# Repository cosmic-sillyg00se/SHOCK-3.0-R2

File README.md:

# SHOCK-3.0-R2
(7/14/2025) I finally discovered manufacturer datasheets! Kudos to past me, I maanaged to cram even more components onto an even smaller board WIHTOUT sacrificing aesthetics. I say this because it didn't work.

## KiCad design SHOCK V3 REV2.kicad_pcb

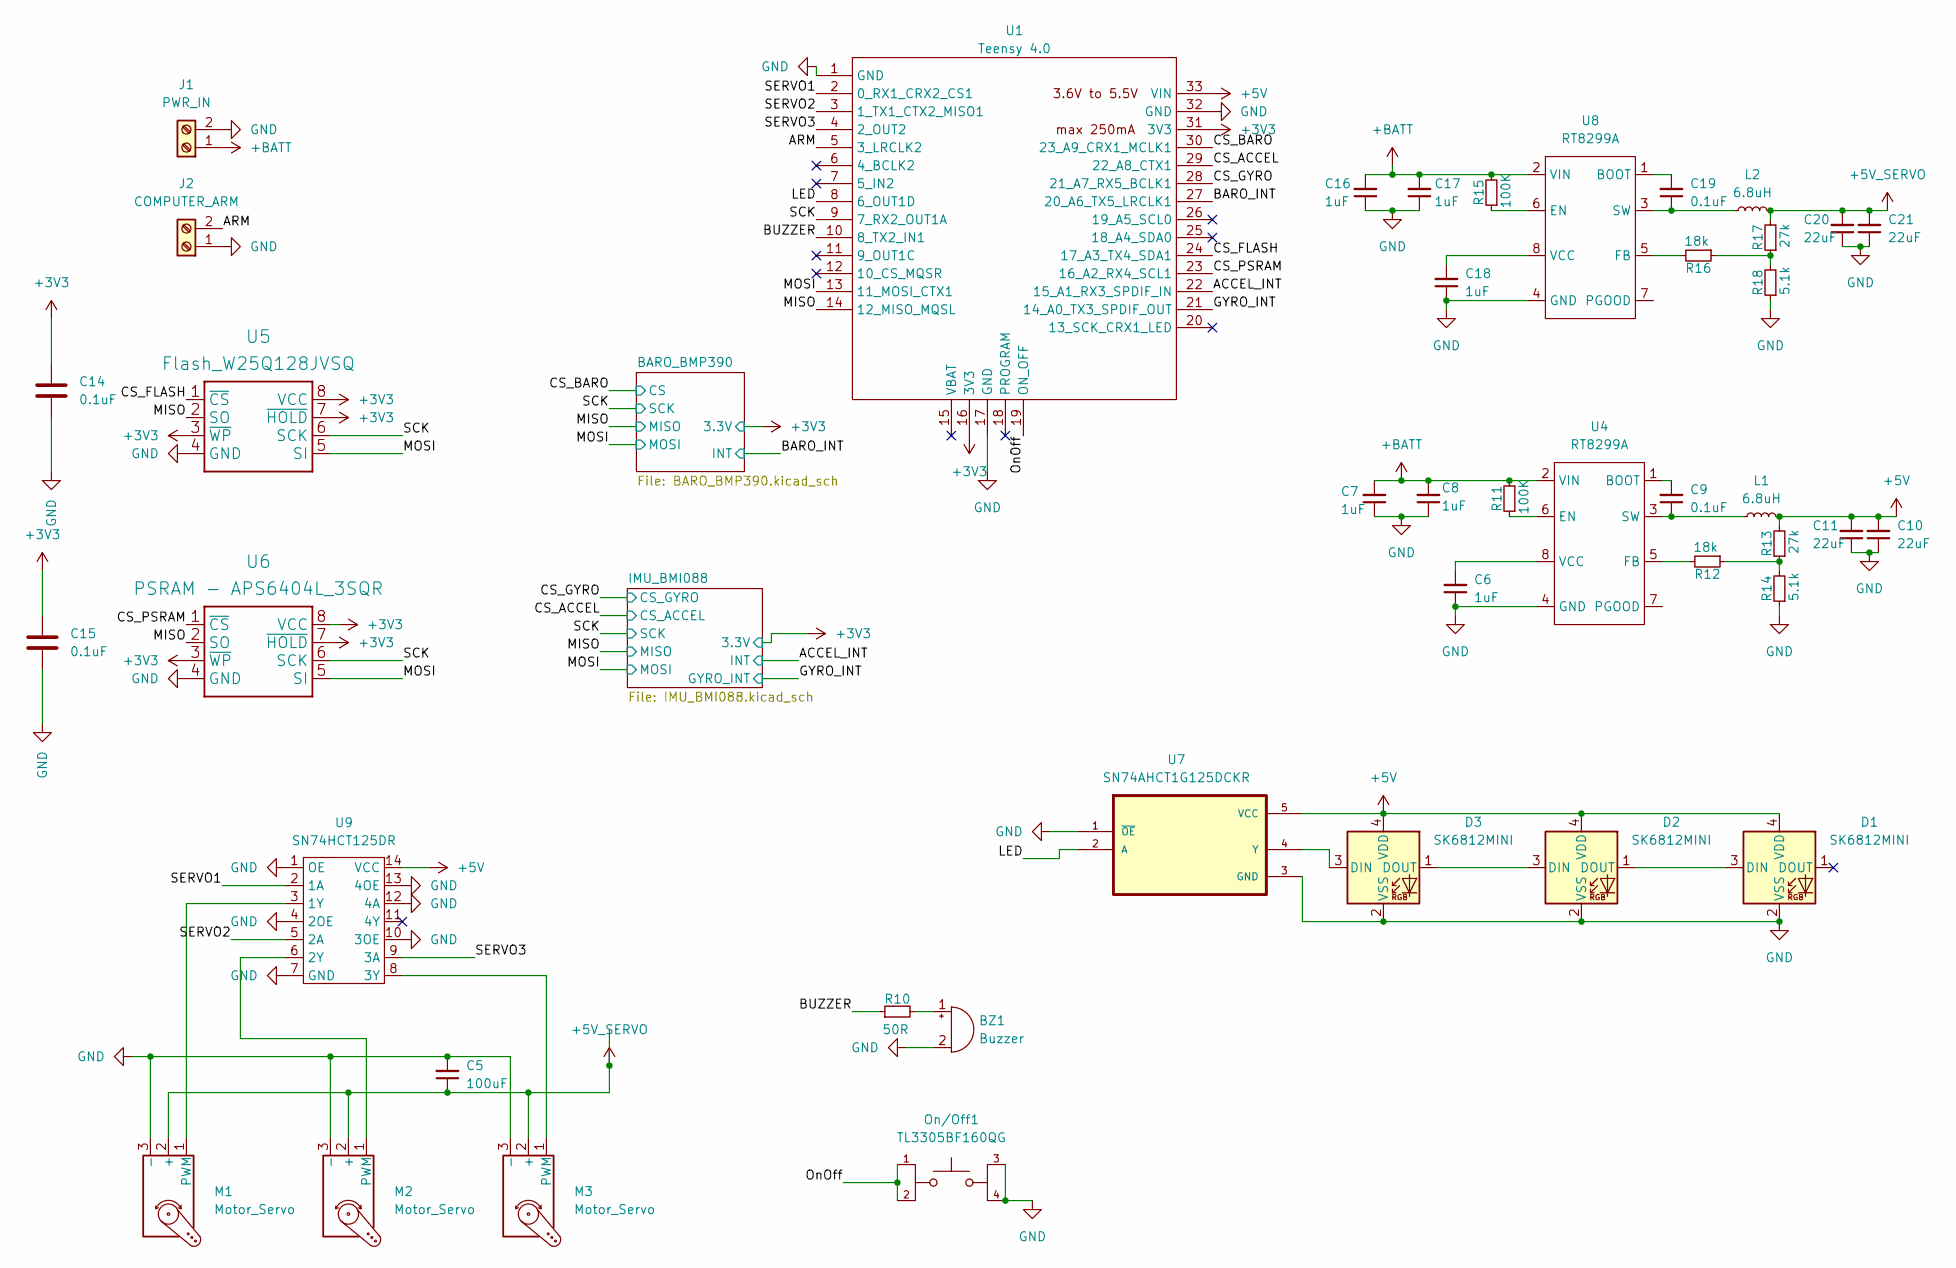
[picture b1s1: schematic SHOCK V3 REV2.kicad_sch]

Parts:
BZ1: Buzzer; Buzzer_TDK_PS1240P02BT_D12.2mm_H6.5mm
C5: 100uF; CP_Elec_8x10.5
C6, C7, C8, C16, C17, C18: 1uF; C_0603_1608Metric_Pad1.08x0.95mm_HandSolder
C9, C14, C15, C19: 0.1uF; C_0603_1608Metric_Pad1.08x0.95mm_HandSolder
C10, C11, C20, C21: 22uF; C_0603_1608Metric_Pad1.08x0.95mm_HandSolder
D1, D2, D3: SK6812MINI; LED_SK6805_PLCC4_2.4x2.7mm_P1.3mm
J1: PWR_IN; TerminalBlock_MaiXu_MX126-5.0-02P_1x02_P5.00mm
J2: COMPUTER_ARM; TerminalBlock_MaiXu_MX126-5.0-02P_1x02_P5.00mm
L1, L2: 6.8uH; L_0603_1608Metric_Pad1.05x0.95mm_HandSolder
M1, M2, M3: Motor_Servo; PinHeader_1x03_P2.54mm_Vertical
On/Off1: TL3305BF160QG; SW_TL3305BF160QG; PARTREV C
R10: 50R; R_0603_1608Metric_Pad0.98x0.95mm_HandSolder
R11, R15: 100K; R_0603_1608Metric_Pad0.98x0.95mm_HandSolder
R12, R16: 18k; R_0603_1608Metric_Pad0.98x0.95mm_HandSolder
R13, R17: 27k; R_0603_1608Metric_Pad0.98x0.95mm_HandSolder
R14, R18: 5.1k; R_0603_1608Metric_Pad0.98x0.95mm_HandSolder
U1: Teensy 4.0; Teensy4.0
U4, U8: RT8299A; SOIC-8_5.3x6.2mm_P1.27mm
U5: Flash_W25Q128JVSQ; SOIC127P790X216-8N
U6: PSRAM - APS6404L_3SQR; SOIC127P790X216-8N
U7: SN74AHCT1G125DCKR; SOT65P210X110-5N
U9: SN74HCT125DR; SOIC-14_3.9x8.7mm_P1.27mm

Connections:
+3V3: C14.1, C15.1, U1.16 (3V3), U1.31 (3V3), U5.3 (~WP), U5.7 (~HOLD), U5.8 (VCC), U6.3 (~WP), U6.7 (~HOLD), U6.8 (VCC); also elsewhere on the board
+5V: C10.2, C11.2, D1.4 (VDD), D2.4 (VDD), D3.4 (VDD), L1.2, R13.2, U1.33 (VIN), U7.5 (VCC), U9.14 (VCC)
+5V_SERVO: C5.1, C20.2, C21.2, L2.2, M1.2 (+), M2.2 (+), M3.2 (+), R17.2
+BATT: C7.2, C8.2, C16.2, C17.2, J1.1, R11.2, R15.2, U4.2 (VIN), U8.2 (VIN)
/ACCEL_INT: U1.22 (15_A1_RX3_SPDIF_IN); also elsewhere on the board
/ARM: J2.2, U1.5 (3_LRCLK2)
/BARO_INT: U1.27 (20_A6_TX5_LRCLK1); also elsewhere on the board
/BUZZER: R10.1, U1.10 (8_TX2_IN1)
/CS_ACCEL: U1.29 (22_A8_CTX1); also elsewhere on the board
/CS_BARO: U1.30 (23_A9_CRX1_MCLK1); also elsewhere on the board
/CS_FLASH: U1.24 (17_A3_TX4_SDA1), U5.1 (~CS)
/CS_GYRO: U1.28 (21_A7_RX5_BCLK1); also elsewhere on the board
/CS_PSRAM: U1.23 (16_A2_RX4_SCL1), U6.1 (~CS)
/GYRO_INT: U1.21 (14_A0_TX3_SPDIF_OUT); also elsewhere on the board
/LED: U1.8 (6_OUT1D), U7.2 (A)
/MISO: U1.14 (12_MISO_MQSL), U5.2 (SO), U6.2 (SO); also elsewhere on the board
/MOSI: U1.13 (11_MOSI_CTX1), U5.5 (SI), U6.5 (SI); also elsewhere on the board
/OnOff: On/Off1.1, On/Off1.2, U1.19 (ON_OFF)
/SCK: U1.9 (7_RX2_OUT1A), U5.6 (SCK), U6.6 (SCK); also elsewhere on the board
/SERVO1: U1.2 (0_RX1_CRX2_CS1), U9.2 (1A)
/SERVO2: U1.3 (1_TX1_CTX2_MISO1), U9.5 (2A)
/SERVO3: U1.4 (2_OUT2), U9.9 (3A)
GND: BZ1.2 (-), C5.2, C6.1, C7.1, C8.1, C10.1, C11.1, C14.2, C15.2, C16.1, C17.1, C18.1, C20.1, C21.1, D1.2 (VSS), D2.2 (VSS), D3.2 (VSS), J1.2, J2.1, M1.3 (-), M2.3 (-), M3.3 (-), On/Off1.3, On/Off1.4, R14.1, R18.1, U1.1 (GND), U1.17 (GND), U1.32 (GND), U4.4 (GND), U5.4 (GND), U6.4 (GND), U7.1 (~OE), U7.3 (GND), U8.4 (GND), U9.1 (OE), U9.4 (2OE), U9.7 (GND), U9.10 (3OE), U9.12 (4A), U9.13 (4OE); also elsewhere on the board
unnamed: BZ1.1 (+), R10.2
unnamed: D1.3 (DIN), D2.1 (DOUT)
unnamed: D2.3 (DIN), D3.1 (DOUT)
unnamed: D3.3 (DIN), U7.4 (Y)
unnamed: M1.1 (PWM), U9.3 (1Y)
unnamed: M2.1 (PWM), U9.6 (2Y)
unnamed: M3.1 (PWM), U9.8 (3Y)
unnamed: R12.1, R13.1, R14.2
unnamed: R16.1, R17.1, R18.2
unnamed: C9.2, U4.1 (BOOT)
unnamed: R11.1, U4.6 (EN)
unnamed: R12.2, U4.5 (FB)
unnamed: C9.1, L1.1, U4.3 (SW)
unnamed: C6.2, U4.8 (VCC)
unnamed: C19.2, U8.1 (BOOT)
unnamed: R15.1, U8.6 (EN)
unnamed: R16.2, U8.5 (FB)
unnamed: C19.1, L2.1, U8.3 (SW)
unnamed: C18.2, U8.8 (VCC)

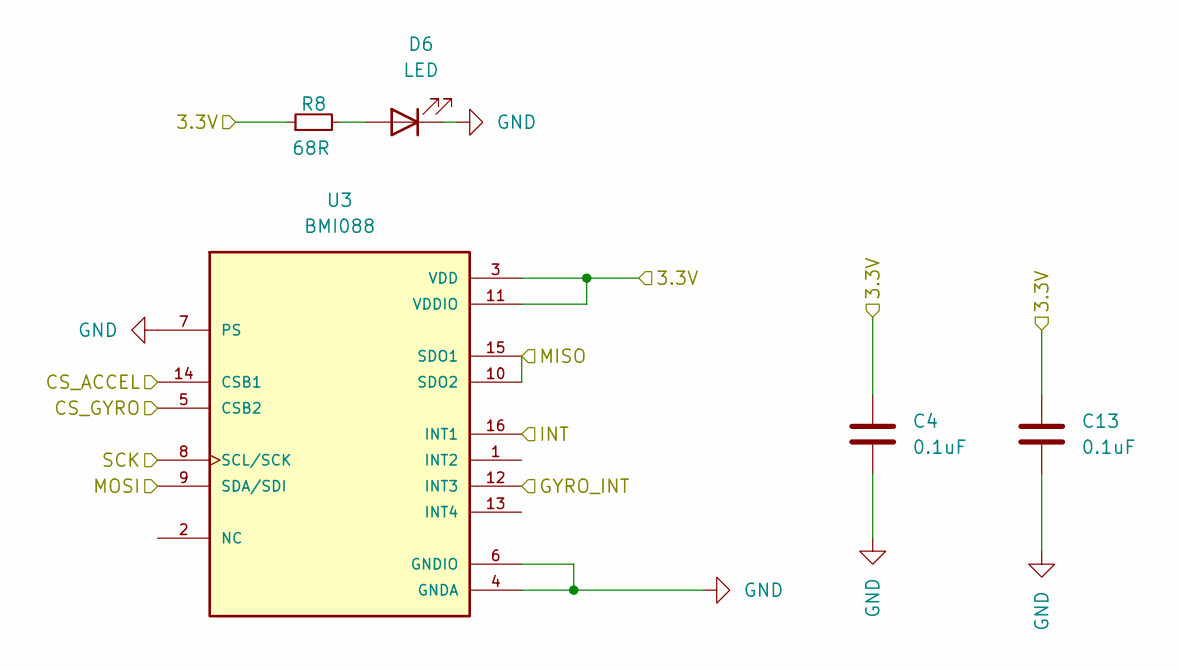
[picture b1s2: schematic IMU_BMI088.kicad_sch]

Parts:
C4, C13: 0.1uF; C_0603_1608Metric_Pad1.08x0.95mm_HandSolder
D6: LED; LED_0603_1608Metric
R8: 68R; R_0603_1608Metric_Pad0.98x0.95mm_HandSolder
U3: BMI088; BMI088SMT

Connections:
+3V3: C4.1, C13.1, R8.1, U3.3 (VDD), U3.11 (VDDIO); also elsewhere on the board
/ACCEL_INT: U3.16 (INT1); also elsewhere on the board
/CS_ACCEL: U3.14 (CSB1); also elsewhere on the board
/CS_GYRO: U3.5 (CSB2); also elsewhere on the board
/GYRO_INT: U3.12 (INT3); also elsewhere on the board
/MISO: U3.10 (SDO2), U3.15 (SDO1); also elsewhere on the board
/MOSI: U3.9 (SDA/SDI); also elsewhere on the board
/SCK: U3.8 (SCL/SCK); also elsewhere on the board
GND: C4.2, C13.2, D6.1 (K), U3.4 (GNDA), U3.6 (GNDIO), U3.7 (PS); also elsewhere on the board
unnamed: D6.2 (A), R8.2

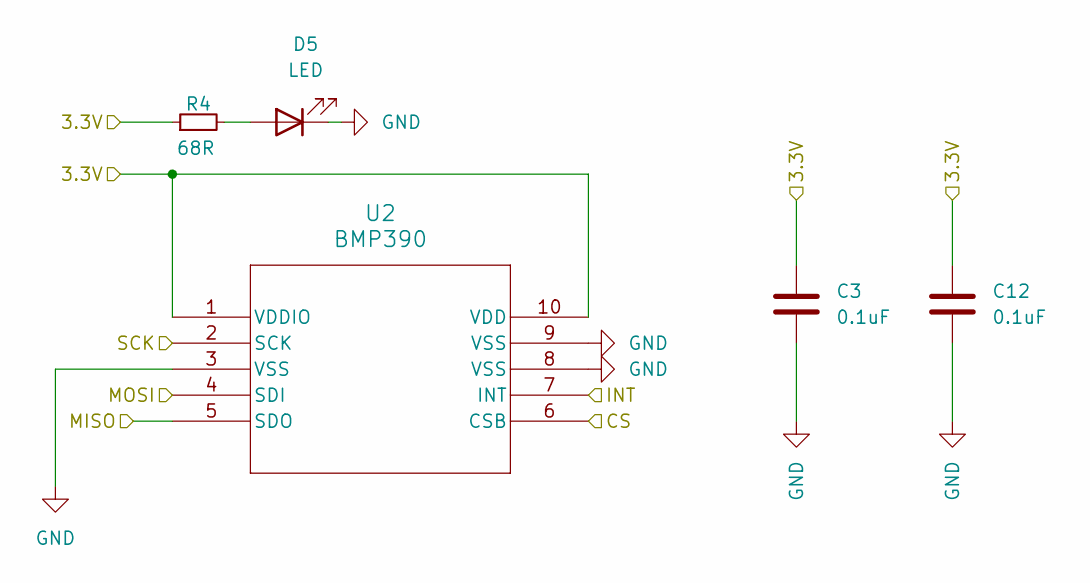
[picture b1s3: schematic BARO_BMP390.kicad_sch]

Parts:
C3, C12: 0.1uF; C_0603_1608Metric_Pad1.08x0.95mm_HandSolder
D5: LED; LED_0603_1608Metric
R4: 68R; R_0603_1608Metric_Pad0.98x0.95mm_HandSolder
U2: BMP390; BMP390SMT

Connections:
+3V3: C3.1, C12.1, R4.1, U2.1 (VDDIO), U2.10 (VDD); also elsewhere on the board
/BARO_INT: U2.7 (INT); also elsewhere on the board
/CS_BARO: U2.6 (CSB); also elsewhere on the board
/MISO: U2.5 (SDO); also elsewhere on the board
/MOSI: U2.4 (SDI); also elsewhere on the board
/SCK: U2.2 (SCK); also elsewhere on the board
GND: C3.2, C12.2, D5.1 (K), U2.3 (VSS), U2.8 (VSS), U2.9 (VSS); also elsewhere on the board
unnamed: D5.2 (A), R4.2

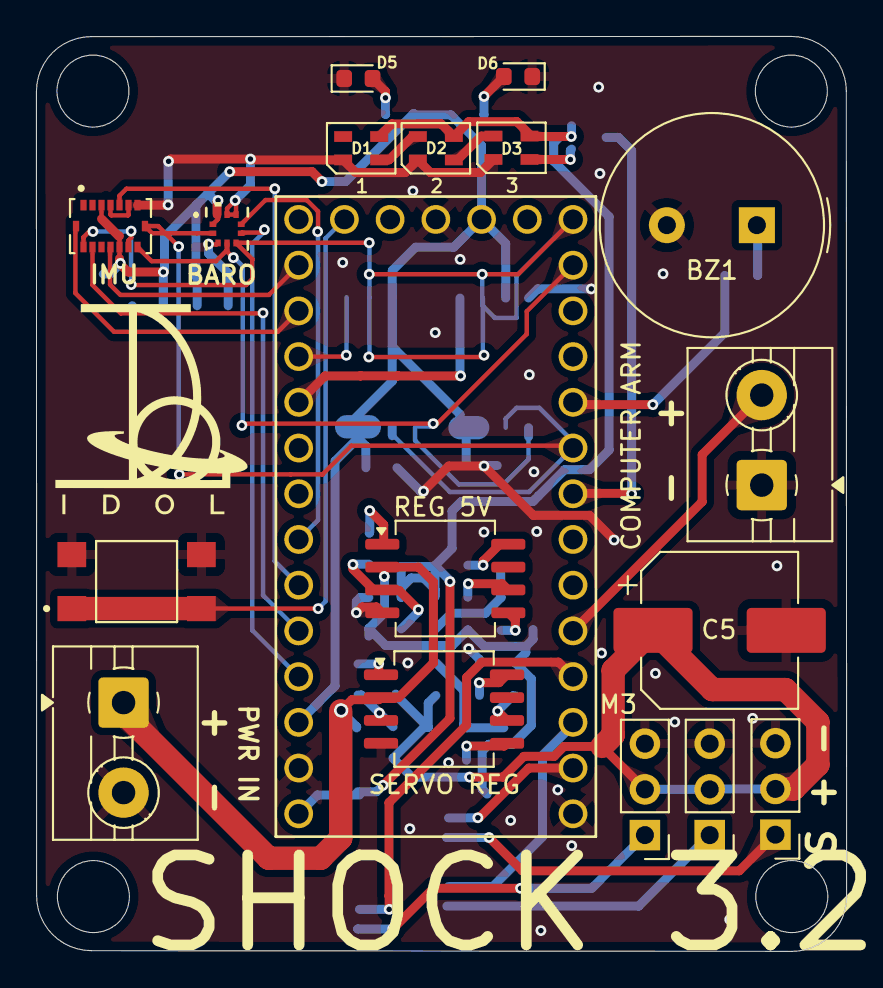
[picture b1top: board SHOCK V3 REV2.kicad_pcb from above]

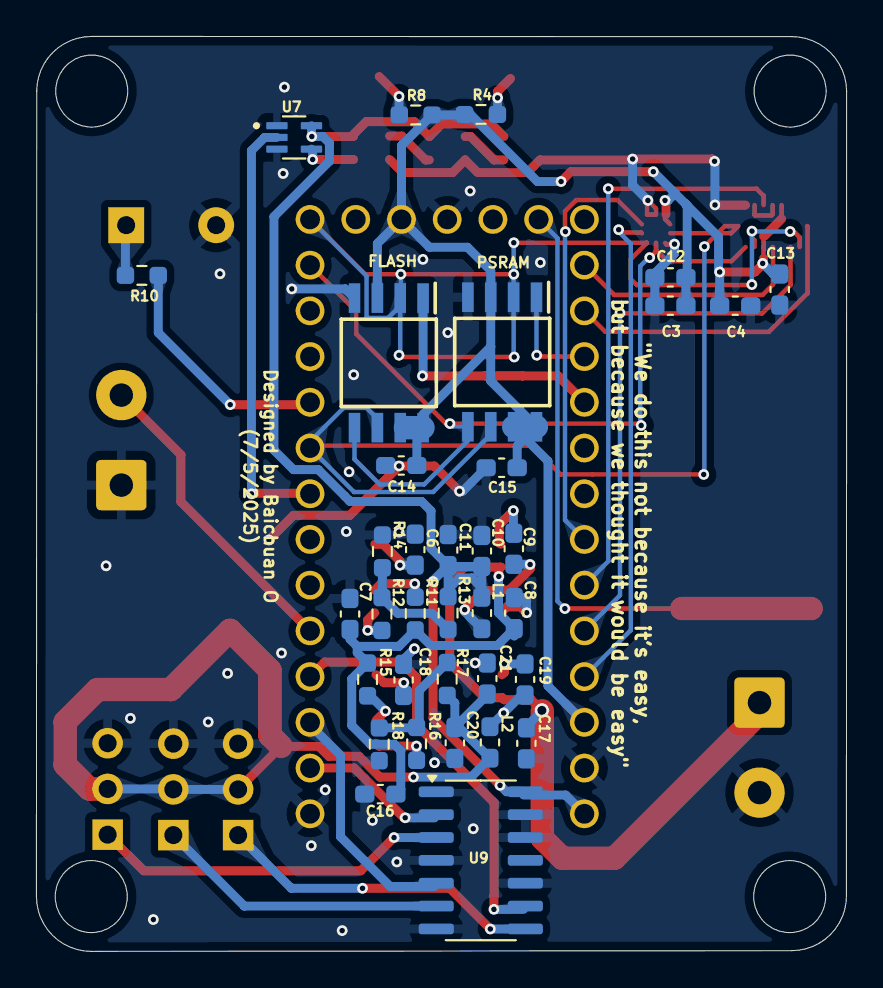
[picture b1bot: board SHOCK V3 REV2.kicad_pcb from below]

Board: 2 copper layers, 45.0 x 50.8 mm, 53 parts (35 on the bottom side), 44 nets.

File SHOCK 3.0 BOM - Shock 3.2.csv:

Type,Value,Quantity,Designator,Package,Digikey Number
MCU,Teensy 4.0,1,U1,,1568-15583-ND
Sensor,BMP390,1,U2,,828-BMP390CT-ND
Sensor,BMI088,1,U3,,828-1082-1-ND 
Converter,RT8299A,2,"U8,U4",,1028-1295-1-ND
Flash,Flash_W25Q128JVSQ,1,U5,,W25Q128JVSIQ-ND
PSRam,PSRAM - APS6404L_3SQR,1,U6,,1528-4677-ND
1 Channel shifter,SN74AHCT1G125DCKR,1,U7,,296-4709-1-ND
4 Channel Shifter,SN74HCT125DR,1,U9,,296-1206-1-ND
Inductor,6.8uH,2,"L2,L1",,445-MLZ1608M6R8WT000CT-ND
Capacitor,0.1uF,8,"C19,C9,C13,C4,C14,C3,C15,C12",,311-1088-1-ND
,1uF,6,"C17,C16,C18,C6,C7,C8",,1276-1946-1-ND
,22uF,4,"C21,C20,C10,C11",,490-10476-1-ND
,100uF,1,C5,,493-6341-1-ND
Resistor,100K,2,"R15,R11",,RG16P100KBCT-ND
,5.1k,2,"R18,R14",,311-5.10KHRCT-ND
,18k,2,"R16,R12",,A129691CT-ND
,27k,2,"R17,R13",,RMCF0603JT27K0CT-ND
,50R,1,R10,,541-3318-1-ND
,68R,2,"R4,R8",,311-68.0HRCT-ND
LED,LED,2,"D5,D6",,846-SML-D12P8WT86CT-ND
RGD LED,SK6812MINI,3,"D1,D2,D3",,1830-1207-1-ND
Button,TL3305BF160QG,1,On/Off1,,141-TL3305BF100QGCT-ND
Terminal,PWR_IN,1,J1,,5441537-ND
Terminal,COMPUTER_ARM,1,J2,,5441537-ND
Buzzer,Buzzer,1,BZ1,,445-2525-1-ND
Servo,Motor_Servo,3,"M2,M3,M1",,

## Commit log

2026-02-05 Added all KiCad files
